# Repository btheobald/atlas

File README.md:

View this project on [CADLAB.io](https://cadlab.io/project/23699). 

# atlas

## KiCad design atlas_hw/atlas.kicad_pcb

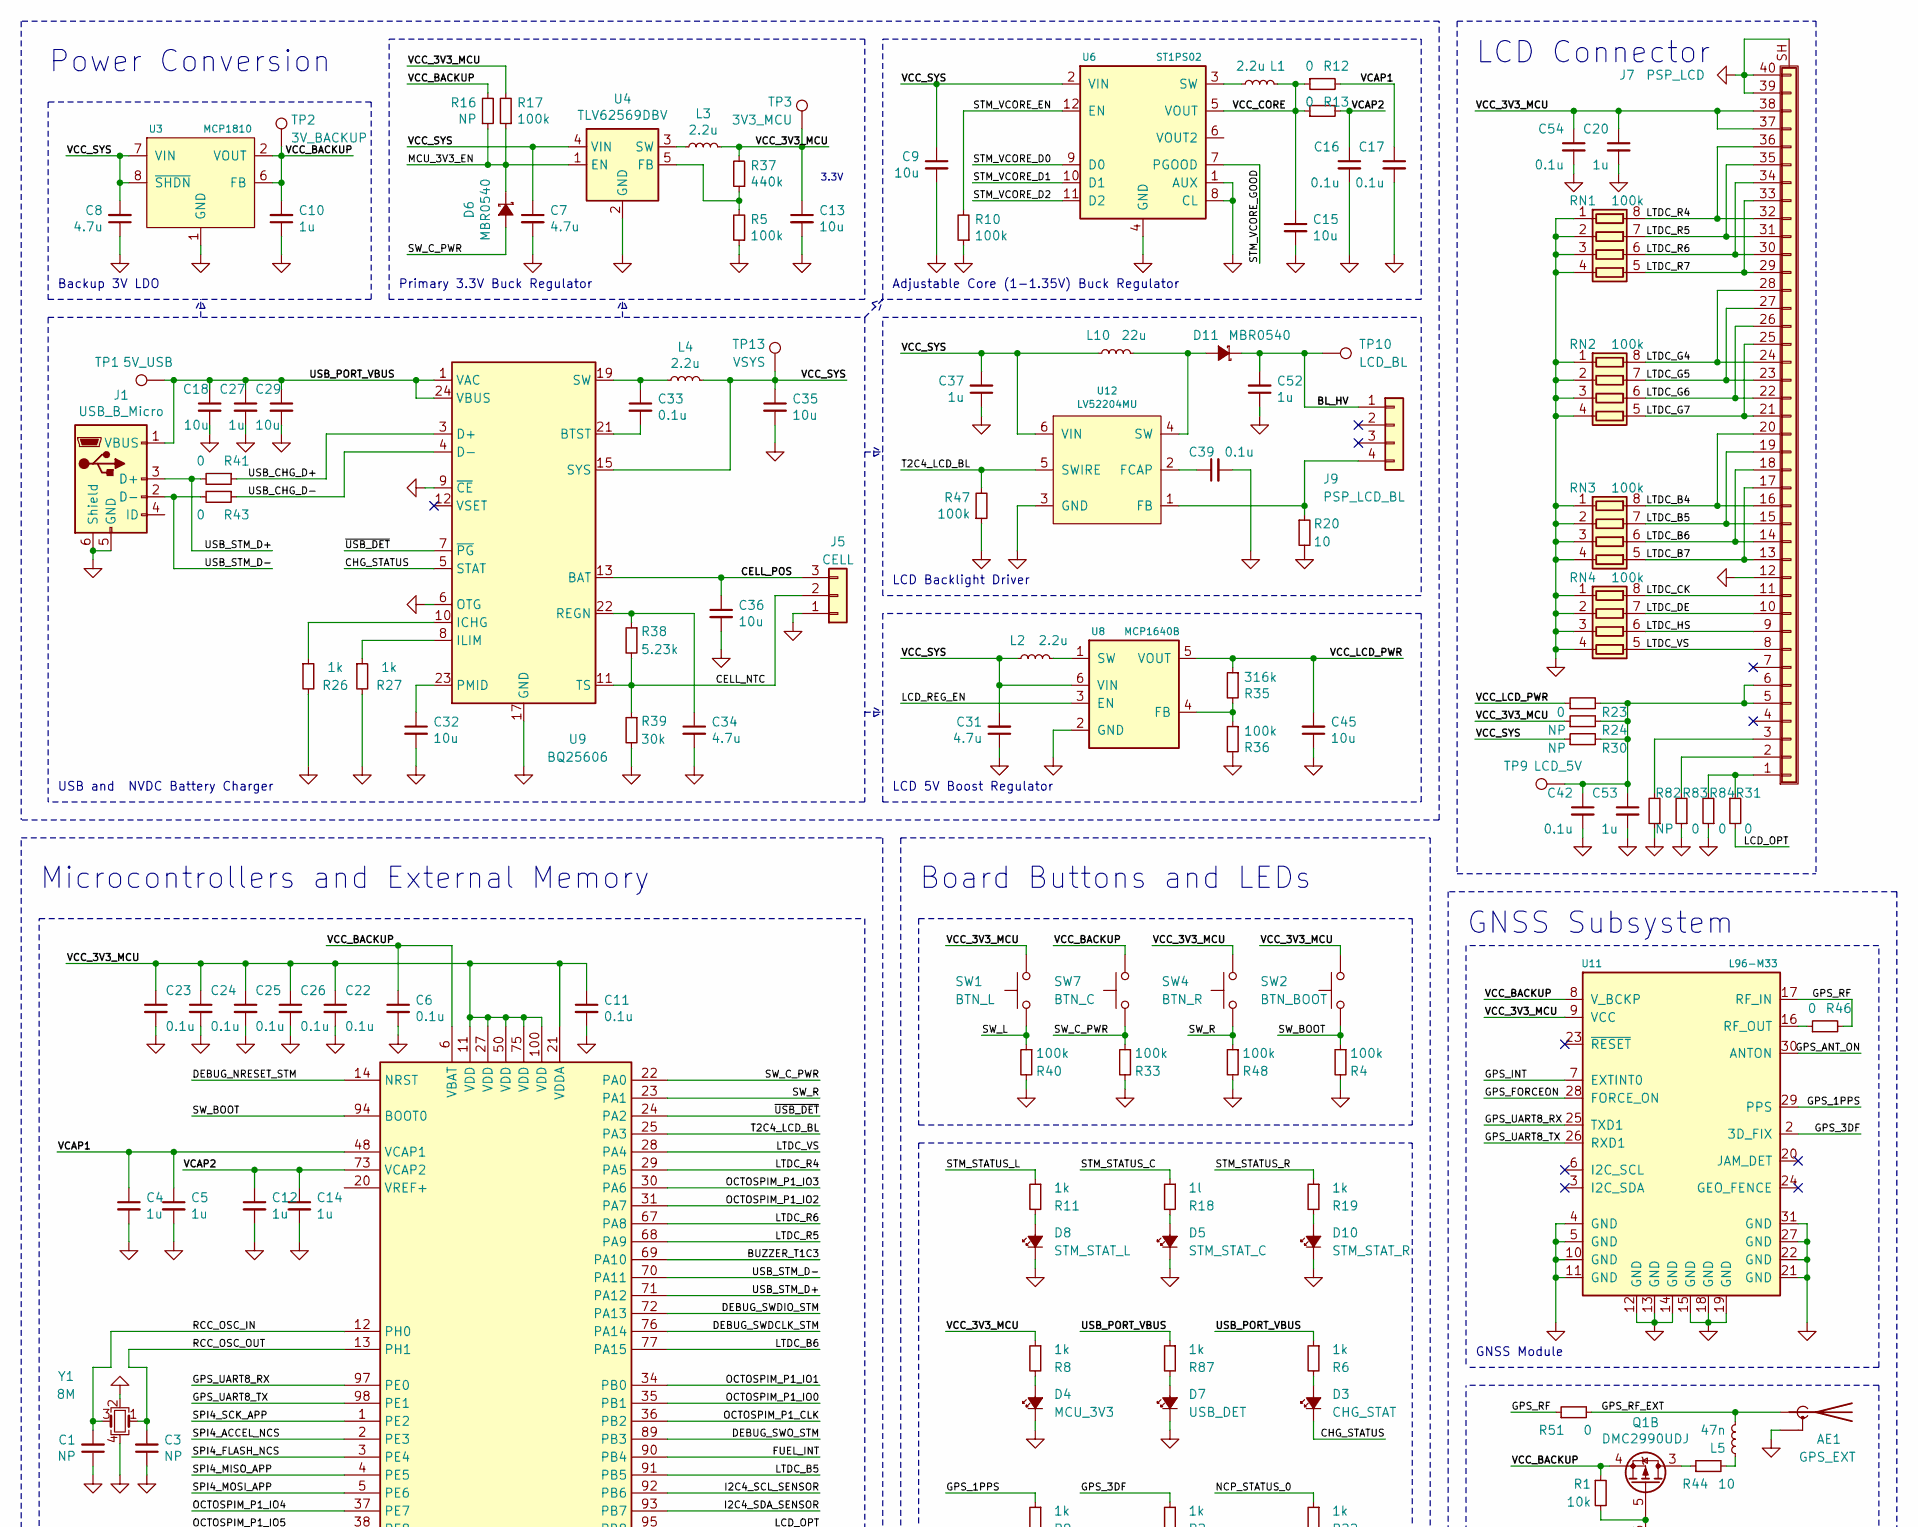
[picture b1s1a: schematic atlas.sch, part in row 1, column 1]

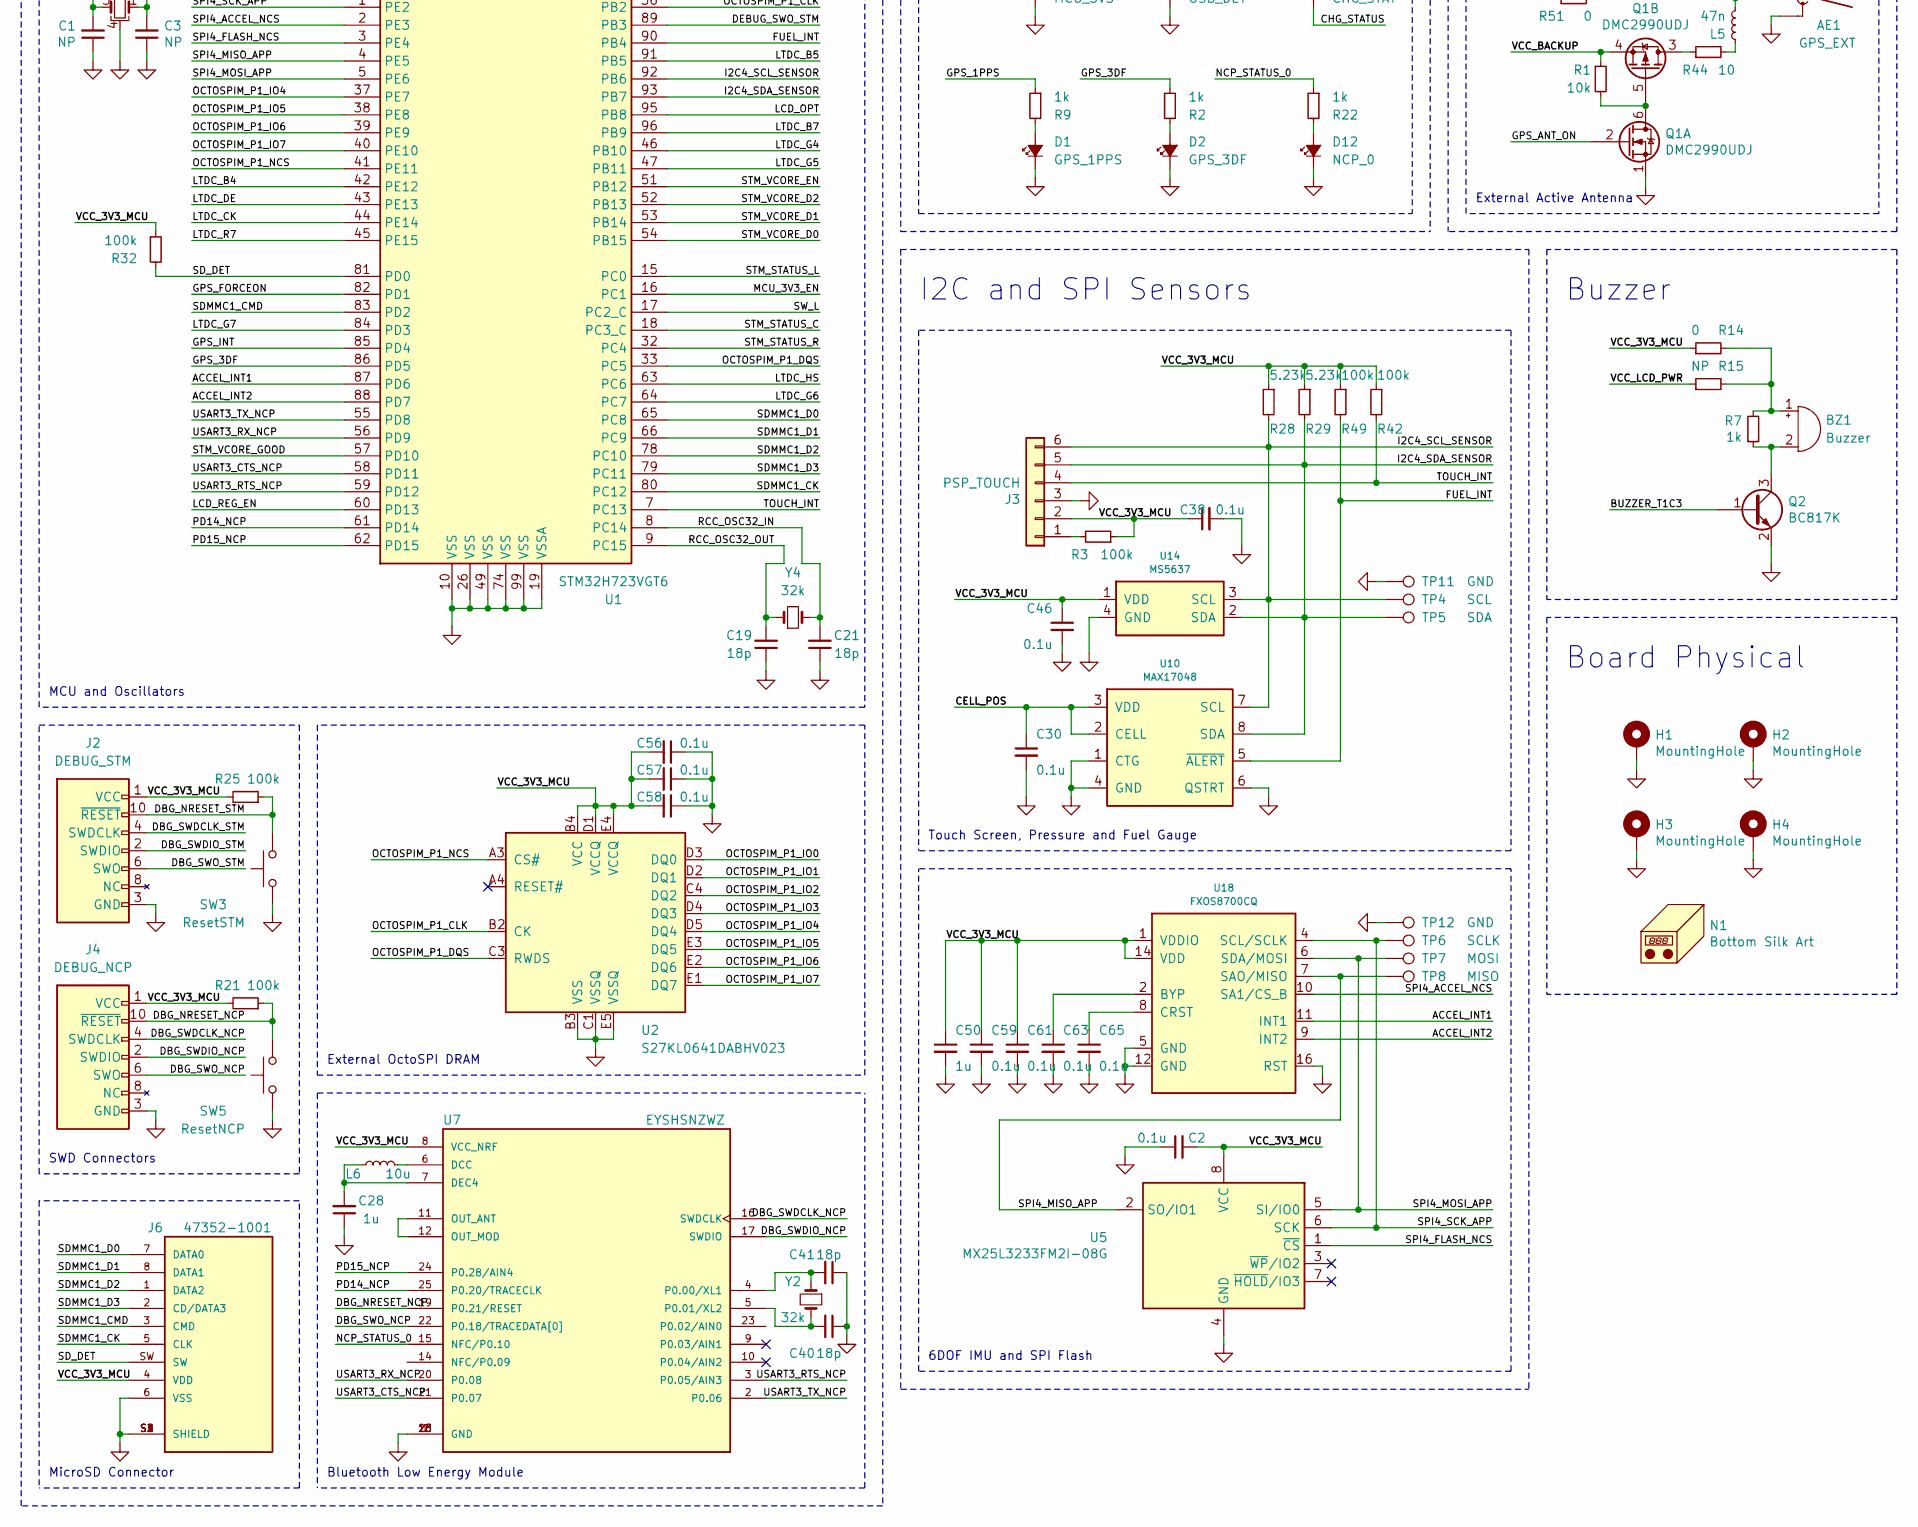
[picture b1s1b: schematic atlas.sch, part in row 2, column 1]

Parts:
AE1: GPS_EXT; U.FL_Hirose_U.FL-R-SMT-1_Vertical
BZ1: Buzzer; PKLCS1212
C1, C3: NP; C_0402_1005Metric
C2, C6, C11, C16, C17, C22, C23, C24, C25, C26, C30, C33, C38, C39, C42, C46, C54, C56, C57, C58, C59, C61, C63, C65: 0.1u; C_0402_1005Metric
C4, C5, C10, C12, C14, C20, C27, C28, C37, C50, C52, C53: 1u; C_0603_1608Metric
C7, C8, C31, C34: 4.7u; C_0805_2012Metric
C9, C13, C15, C18, C29, C32, C35, C36, C45: 10u; C_0805_2012Metric
C19, C21, C40, C41: 18p; C_0402_1005Metric
D1: GPS_1PPS; LED_0805_2012Metric
D2: GPS_3DF; LED_0805_2012Metric
D3: CHG_STAT; LED_0805_2012Metric
D4: MCU_3V3; LED_0805_2012Metric
D5: STM_STAT_C; LED_0805_2012Metric
D6, D11: MBR0540; D_SOD-123
D7: USB_DET; LED_0805_2012Metric
D8: STM_STAT_L; LED_0805_2012Metric
D10: STM_STAT_R; LED_0805_2012Metric
D12: NCP_0; LED_0805_2012Metric
H1, H2, H3, H4: MountingHole; MountingHole_2.2mm_M2_Pad_Via
J1: USB_B_Micro; USB_Micro-B_Molex_47346-0001
J2: DEBUG_STM; PinHeader_2x05_P1.27mm_Vertical_SMD
J3: PSP_TOUCH; TE_2328702-6
J4: DEBUG_NCP; PinHeader_2x05_P1.27mm_Vertical_SMD
J5: CELL; PinHeader_1x03_P1.00mm_Vertical
J6: 47352-1001; MOLEX_47352-1001; PARTREV K
J7: PSP_LCD; J_SMD_4-1734839-0-40_0.5_25.43_5.1_2.05
J9: PSP_LCD_BL; SFV4R-1STE1LF
L1, L2, L3, L4: 2.2u; L_Wuerth_MAPI-2510
L5: 47n; L_0402_1005Metric
L6: 10u; L_Wuerth_MAPI-2510
L10: 22u; L_Bourns-SRN4018
N1: Bottom Silk Art; europeart
Q1: DMC2990UDJ; SOT-363_SC-70-6
Q2: BC817K; SOT-23
R1: 10k; R_0402_1005Metric
R2, R6, R7, R8, R9, R11, R19, R22, R26, R27, R87: 1k; R_0603_1608Metric
R3, R4, R5, R10, R17, R21, R25, R32, R33, R36, R40, R42, R47, R48, R49: 100k; R_0603_1608Metric
R12, R13, R14, R23: 0; SolderJumper-2_P1.3mm_Open_TrianglePad1.0x1.5mm
R15, R24, R30: NP; SolderJumper-2_P1.3mm_Open_TrianglePad1.0x1.5mm
R16: NP; R_0603_1608Metric
R18: 1l; R_0603_1608Metric
R20, R44: 10; R_0603_1608Metric
R28, R29, R38: 5.23k; R_0603_1608Metric
R31, R46, R51, R83, R84: 0; R_0402_1005Metric
R35: 316k; R_0603_1608Metric
R37: 440k; R_0603_1608Metric
R39: 30k; R_0603_1608Metric
R41, R43: 0; R_0603_1608Metric
R82: NP; R_0402_1005Metric
RN1, RN2, RN3, RN4: 100k; R_Array_Concave_4x0402
SW1: BTN_L; SW_SPST_PTS810
SW2: BTN_BOOT; SW_SPST_PTS810
SW3: ResetSTM; SW_SPST_PTS810
SW4: BTN_R; SW_SPST_PTS810
SW5: ResetNCP; SW_SPST_PTS810
SW7: BTN_C; SW_SPST_PTS810
TP1: 5V_USB; TestPoint_THTPad_D1.0mm_Drill0.5mm
TP2: 3V_BACKUP; TestPoint_THTPad_D1.0mm_Drill0.5mm
TP3: 3V3_MCU; TestPoint_THTPad_D1.0mm_Drill0.5mm
TP4: SCL; TestPoint_THTPad_D1.0mm_Drill0.5mm
TP5: SDA; TestPoint_THTPad_D1.0mm_Drill0.5mm
TP6: SCLK; TestPoint_THTPad_D1.0mm_Drill0.5mm
TP7: MOSI; TestPoint_THTPad_D1.0mm_Drill0.5mm
TP8: MISO; TestPoint_THTPad_D1.0mm_Drill0.5mm
TP9: LCD_5V; TestPoint_THTPad_D1.0mm_Drill0.5mm
TP10: LCD_BL; TestPoint_THTPad_D1.0mm_Drill0.5mm
TP11, TP12: GND; TestPoint_THTPad_D1.0mm_Drill0.5mm
TP13: VSYS; TestPoint_THTPad_D1.0mm_Drill0.5mm
U1: STM32H723VGT6; LQFP-100_14x14mm_P0.5mm
U2: S27KL0641DABHV023; BGA-25_5x5_6.0x8.0mm
U3: MCP1810; DFN-8-1EP_2x2mm_P0.5mm_EP0.9x1.5mm
U4: TLV62569DBV; SOT-23-5
U5: MX25L3233FM2I-08G; SSOP-8_5.25x5.24mm_P1.27mm
U6: ST1PS02; TQFN-12_1.7x2.0mm_P0.4mm
U7: EYSHSNZWZ; XCVR_EYSHSNZWZ; PARTREV 1.2
U8: MCP1640B; SOT-23-6
U9: BQ25606; WQFN-24-1EP_4x4mm_P0.5mm_EP2.7x2.7mm
U10: MAX17048; DFN-8-1EP_2x2mm_P0.5mm_EP0.9x1.5mm
U11: L96-M33; L96
U12: LV52204MU; DFN-6-1EP_2x2mm_P0.65mm_EP1x1.6mm
U14: MS5637; QFN-4_3x3_Pitch2mm
U18: FXOS8700CQ; LGA-16_3x3mm_P0.5mm_LayoutBorder3x5y
Y1: 8M; Crystal_SMD_3225-4Pin_3.2x2.5mm
Y2, Y4: 32k; Crystal_SMD_MicroCrystal_CC7V-T1A-2Pin_3.2x1.5mm

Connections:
/ACCEL_INT1: U1.87 (PD6), U18.11 (INT1)
/ACCEL_INT2: U1.88 (PD7), U18.9 (INT2)
/BL_HV: C52.2, D11.1 (K), J9.1, TP10.1
/BUZZER_T1C3: Q2.1 (B), U1.69 (PA10)
/CELL_NTC: J5.2, R38.2, R39.1, U9.11 (TS)
/CELL_POS: C30.1, C36.1, J5.3, U9.13 (BAT), U9.14 (BAT), U10.2 (CELL), U10.3 (VDD)
/CHG_STATUS: D3.1 (K), U9.5 (STAT)
/DBG_NRESET_NCP: J4.10 (~RESET~), R21.1, SW5.1, U7.19 (P0.21/RESET)
/DBG_NRESET_STM: J2.10 (~RESET~), R25.1, SW3.1
/DBG_SWDCLK_NCP: J4.4 (SWDCLK), U7.16 (SWDCLK)
/DBG_SWDCLK_STM: J2.4 (SWDCLK)
/DBG_SWDIO_NCP: J4.2 (SWDIO), U7.17 (SWDIO)
/DBG_SWDIO_STM: J2.2 (SWDIO)
/DBG_SWO_NCP: J4.6 (SWO), U7.22 (P0.18/TRACEDATA[0])
/DBG_SWO_STM: J2.6 (SWO)
/DEBUG_NRESET_STM: U1.14 (NRST)
/DEBUG_SWDCLK_STM: U1.76 (PA14)
/DEBUG_SWDIO_STM: U1.72 (PA13)
/DEBUG_SWO_STM: U1.89 (PB3)
/FUEL_INT: R49.2, U1.90 (PB4), U10.5 (~ALERT)
/GPS_1PPS: R9.1, U11.29 (PPS)
/GPS_3DF: R2.1, U1.86 (PD5), U11.2 (3D_FIX)
/GPS_ANT_ON: Q1.2 (G), U11.30 (ANTON)
/GPS_FORCEON: U1.82 (PD1), U11.28 (FORCE_ON)
/GPS_INT: U1.85 (PD4), U11.7 (EXTINT0)
/GPS_RF: R46.2, R51.1, U11.17 (RF_IN)
/GPS_RF_EXT: AE1.1 (A), L5.1, R51.2
/GPS_UART8_RX: U1.97 (PE0), U11.25 (TXD1)
/GPS_UART8_TX: U1.98 (PE1), U11.26 (RXD1)
/I2C4_SCL_SENSOR: J3.6, R28.2, TP4.1, U1.92 (PB6), U10.7 (SCL), U14.3 (SCL)
/I2C4_SDA_SENSOR: J3.5, R29.2, TP5.1, U1.93 (PB7), U10.8 (SDA), U14.2 (SDA)
/LCD_OPT: R31.2, U1.95 (PB8)
/LCD_REG_EN: U1.60 (PD13), U8.3 (EN)
/LTDC_B4: J7.16, J7.20, RN3.8 (R1.2), U1.42 (PE12)
/LTDC_B5: J7.15, J7.19, RN3.7 (R2.2), U1.91 (PB5)
/LTDC_B6: J7.14, J7.18, RN3.6 (R3.2), U1.77 (PA15)
/LTDC_B7: J7.13, J7.17, RN3.5 (R4.2), U1.96 (PB9)
/LTDC_CK: J7.11, RN4.8 (R1.2), U1.44 (PE14)
/LTDC_DE: J7.10, RN4.7 (R2.2), U1.43 (PE13)
/LTDC_G4: J7.24, J7.28, RN2.8 (R1.2), U1.46 (PB10)
/LTDC_G5: J7.23, J7.27, RN2.7 (R2.2), U1.47 (PB11)
/LTDC_G6: J7.22, J7.26, RN2.6 (R3.2), U1.64 (PC7)
/LTDC_G7: J7.21, J7.25, RN2.5 (R4.2), U1.84 (PD3)
/LTDC_HS: J7.9, RN4.6 (R3.2), U1.63 (PC6)
/LTDC_R4: J7.32, J7.36, RN1.8 (R1.2), U1.29 (PA5)
/LTDC_R5: J7.31, J7.35, RN1.7 (R2.2), U1.68 (PA9)
/LTDC_R6: J7.30, J7.34, RN1.6 (R3.2), U1.67 (PA8)
/LTDC_R7: J7.29, J7.33, RN1.5 (R4.2), U1.45 (PE15)
/LTDC_VS: J7.8, RN4.5 (R4.2), U1.28 (PA4)
/MCU_3V3_EN: D6.1 (K), R16.1, R17.1, U1.16 (PC1), U4.1 (EN)
/NCP_STATUS_0: R22.1, U7.15 (NFC/P0.10)
/OCTOSPIM_P1_CLK: U1.36 (PB2), U2.B2 (CK)
/OCTOSPIM_P1_DQS: U1.33 (PC5), U2.C3 (RWDS)
/OCTOSPIM_P1_IO0: U1.35 (PB1), U2.D3 (DQ0)
/OCTOSPIM_P1_IO1: U1.34 (PB0), U2.D2 (DQ1)
/OCTOSPIM_P1_IO2: U1.31 (PA7), U2.C4 (DQ2)
/OCTOSPIM_P1_IO3: U1.30 (PA6), U2.D4 (DQ3)
/OCTOSPIM_P1_IO4: U1.37 (PE7), U2.D5 (DQ4)
/OCTOSPIM_P1_IO5: U1.38 (PE8), U2.E3 (DQ5)
/OCTOSPIM_P1_IO6: U1.39 (PE9), U2.E2 (DQ6)
/OCTOSPIM_P1_IO7: U1.40 (PE10), U2.E1 (DQ7)
/OCTOSPIM_P1_NCS: U1.41 (PE11), U2.A3 (CS#)
/PD14_NCP: U1.61 (PD14), U7.25 (P0.20/TRACECLK)
/PD15_NCP: U1.62 (PD15), U7.24 (P0.28/AIN4)
/RCC_OSC32_IN: C21.2, U1.8 (PC14), Y4.2
/RCC_OSC32_OUT: C19.2, U1.9 (PC15), Y4.1
/RCC_OSC_IN: C1.2, U1.12 (PH0), Y1.3
/RCC_OSC_OUT: C3.2, U1.13 (PH1), Y1.1
/SDMMC1_CK: J6.5 (CLK), U1.80 (PC12)
/SDMMC1_CMD: J6.3 (CMD), U1.83 (PD2)
/SDMMC1_D0: J6.7 (DATA0), U1.65 (PC8)
/SDMMC1_D1: J6.8 (DATA1), U1.66 (PC9)
/SDMMC1_D2: J6.1 (DATA2), U1.78 (PC10)
/SDMMC1_D3: J6.2 (CD/DATA3), U1.79 (PC11)
/SD_DET: J6.SW, R32.2, U1.81 (PD0)
/SPI4_ACCEL_NCS: U1.2 (PE3), U18.10 (SA1/CS_B)
/SPI4_FLASH_NCS: U1.3 (PE4), U5.1 (~CS)
/SPI4_MISO_APP: TP8.1, U1.4 (PE5), U5.2 (SO/IO1), U18.7 (SAO/MISO)
/SPI4_MOSI_APP: TP7.1, U1.5 (PE6), U5.5 (SI/IO0), U18.6 (SDA/MOSI)
/SPI4_SCK_APP: TP6.1, U1.1 (PE2), U5.6 (SCK), U18.4 (SCL/SCLK)
/STM_STATUS_C: R18.1, U1.18 (PC3_C)
/STM_STATUS_L: R11.1, U1.15 (PC0)
/STM_STATUS_R: R19.1, U1.32 (PC4)
/STM_VCORE_D0: U1.54 (PB15), U6.9 (D0)
/STM_VCORE_D1: U1.53 (PB14), U6.10 (D1)
/STM_VCORE_D2: U1.52 (PB13), U6.11 (D2)
/STM_VCORE_EN: R10.2, U1.51 (PB12), U6.12 (EN)
/STM_VCORE_GOOD: U1.57 (PD10), U6.7 (PGOOD)
/SW_BOOT: R4.1, SW2.2, U1.94 (BOOT0)
/SW_C_PWR: D6.2 (A), R33.1, SW7.2, U1.22 (PA0)
/SW_L: R40.1, SW1.2, U1.17 (PC2_C)
/SW_R: R48.1, SW4.2, U1.23 (PA1)
/T2C4_LCD_BL: R47.2, U1.25 (PA3), U12.5 (SWIRE)
/TOUCH_INT: J3.4, R42.2, U1.7 (PC13)
/USART3_CTS_NCP: U1.58 (PD11), U7.21 (P0.07)
/USART3_RTS_NCP: U1.59 (PD12), U7.3 (P0.05/AIN3)
/USART3_RX_NCP: U1.56 (PD9), U7.20 (P0.08)
/USART3_TX_NCP: U1.55 (PD8), U7.2 (P0.06)
/USB_CHG_D+: R41.1, U9.3 (D+)
/USB_CHG_D-: R43.1, U9.4 (D-)
/USB_PORT_VBUS: C18.1, C27.1, C29.1, J1.1 (VBUS), R6.1, R87.1, TP1.1, U9.1 (VAC), U9.24 (VBUS)
/USB_STM_D+: J1.3 (D+), R41.2, U1.71 (PA12)
/USB_STM_D-: J1.2 (D-), R43.2, U1.70 (PA11)
/VCAP1: C4.1, C5.1, C17.1, R12.2, U1.48 (VCAP1)
/VCAP2: C12.1, C14.1, C16.1, R13.2, U1.73 (VCAP2)
/VCC_3V3_MCU: C2.2, C11.1, C13.1, C20.1, C22.1, C23.1, C24.1, C25.1, C26.1, C38.1, C46.1, C50.1, C54.1, C56.2, C57.2, C58.2, C59.1, C61.1, J2.1 (VCC), J3.2, J4.1 (VCC), J6.4 (VDD), J7.37, J7.38, L3.2, R3.1, R8.1, R14.1, R17.2, R21.2, R24.1, R25.2, R28.1, R29.1, R32.1, R37.2, R42.1, R49.1, SW1.1, SW2.1, SW4.1, TP3.1, U1.11 (VDD), U1.21 (VDDA), U1.27 (VDD), U1.50 (VDD), U1.75 (VDD), U1.100 (VDD), U2.B4 (VCC), U2.D1 (VCCQ), U2.E4 (VCCQ), U5.8 (VCC), U7.8 (VCC_NRF), U11.9 (VCC), U14.1 (VDD), U18.1 (VDDIO), U18.14 (VDD)
/VCC_BACKUP: C6.1, C10.2, Q1.4 (S), R1.1, R16.2, SW7.1, TP2.1, U1.6 (VBAT), U3.2 (VOUT), U3.6 (FB), U11.8 (V_BCKP)
/VCC_CORE: C15.1, L1.2, R12.1, R13.1, U6.5 (VOUT)
/VCC_LCD_PWR: C45.2, R15.1, R23.1, R35.1, U8.5 (VOUT)
/VCC_SYS: C7.1, C8.2, C9.1, C31.2, C35.1, C37.2, L2.1, L4.2, L10.1, R30.1, TP13.1, U3.7 (VIN), U3.8 (~SHDN), U4.4 (VIN), U6.2 (VIN), U8.6 (VIN), U9.15 (SYS), U9.16 (SYS), U12.6 (VIN)
/~USB_DET: U1.24 (PA2), U9.7 (~PG)
GND: AE1.2 (Shield), C1.1, C2.1, C3.1, C4.2, C5.2, C6.2, C7.2, C8.1, C9.2, C10.1, C11.2, C12.2, C13.2, C14.2, C15.2, C16.2, C17.2, C18.2, C19.1, C20.2, C21.1, C22.2, C23.2, C24.2, C25.2, C26.2, C27.2, C28.1, C29.2, C30.2, C31.1, C32.2, C34.2, C35.2, C36.2, C37.1, C38.2, C39.2, C40.1, C41.1, C42.2, C45.1, C46.2, C50.2, C52.1, C53.2, C54.2, C56.1, C57.1, C58.1, C59.2, C61.2, C63.2, C65.2, D1.1 (K), D2.1 (K), D4.1 (K), D5.1 (K), D7.1 (K), D8.1 (K), D10.1 (K), D12.1 (K), H1.1, H2.1, H3.1, H4.1, J1.5 (GND), J1.6 (Shield), J2.3 (GND), J2.5 (GND), J2.9 (GND), J3.3, J4.3 (GND), J4.5 (GND), J4.9 (GND), J5.1, J6.6 (VSS), J6.S1 (SHIELD), J6.S2 (SHIELD), J6.S3 (SHIELD), J6.S4 (SHIELD), J7.12, J7.39, J7.40, J7.SH (Shield), Q1.1 (S), Q2.2 (E), R4.2, R5.1, R10.1, R20.2, R26.2, R27.2, R33.2, R36.2, R39.2, R40.2, R47.1, R48.2, R82.1, R83.1, R84.1, RN1.1 (R1.1), RN1.2 (R2.1), RN1.3 (R3.1), RN1.4 (R4.1), RN2.1 (R1.1), RN2.2 (R2.1), RN2.3 (R3.1), RN2.4 (R4.1), RN3.1 (R1.1), RN3.2 (R2.1), RN3.3 (R3.1), RN3.4 (R4.1), RN4.1 (R1.1), RN4.2 (R2.1), RN4.3 (R3.1), RN4.4 (R4.1), SW3.2, SW5.2, TP11.1, TP12.1, U1.10 (VSS), U1.19 (VSSA), U1.26 (VSS), U1.49 (VSS), U1.74 (VSS), U1.99 (VSS), U2.B3 (VSS), U2.C1 (VSSQ), U2.E5 (VSSQ), U3.1 (GND), U3.9 (EP), U4.2 (GND), U5.4 (GND), U6.1 (AUX), U6.4 (GND), U6.8 (CL), U7.1 (GND), U7.13 (GND), U7.18 (GND), U7.26 (GND), U8.2 (GND), U9.6 (OTG), U9.9 (~CE), U9.17 (GND), U9.25 (GND), U10.1 (CTG), U10.4 (GND), U10.6 (QSTRT), U10.9 (PAD), U11.4 (GND), U11.5 (GND), U11.10 (GND), U11.11 (GND), U11.12 (GND), U11.13 (GND), U11.14 (GND), U11.15 (GND), U11.18 (GND), U11.19 (GND), U11.21 (GND), U11.22 (GND), U11.27 (GND), U11.31 (GND), U12.3 (GND), U12.7 (PAD), U14.4 (GND), U18.3 (f), U18.5 (GND), U18.12 (GND), U18.13 (RESERVED)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
unnamed: BZ1.1 (-), R7.2, R14.2, R15.2
unnamed: BZ1.2 (+), Q2.3 (C), R7.1
unnamed: C28.2, L6.1, U7.7 (DEC4)
unnamed: C32.1, U9.23 (PMID)
unnamed: C33.1, L4.1, U9.19 (SW), U9.20 (SW)
unnamed: C33.2, U9.21 (BTST)
unnamed: C34.1, R38.1, U9.22 (REGN)
unnamed: C39.1, U12.2 (FCAP)
unnamed: C40.2, U7.5 (P0.01/XL2), Y2.2
unnamed: C41.2, U7.4 (P0.00/XL1), Y2.1
unnamed: C42.1, C53.1, J7.5, J7.6, R23.2, R24.2, R30.2, TP9.1
unnamed: C63.1, U18.2 (BYP)
unnamed: C65.1, U18.8 (CRST)
unnamed: D1.2 (A), R9.2
unnamed: D2.2 (A), R2.2
unnamed: D3.2 (A), R6.2
unnamed: D4.2 (A), R8.2
unnamed: D5.2 (A), R18.2
unnamed: D7.2 (A), R87.2
unnamed: D8.2 (A), R11.2
unnamed: D10.2 (A), R19.2
unnamed: D11.2 (A), L10.2, U12.4 (SW)
unnamed: D12.2 (A), R22.2
unnamed: J3.1, R3.2
unnamed: J7.1, R31.1, R84.2
unnamed: J7.2, R83.2
unnamed: J7.3, R82.2
unnamed: J9.4, R20.1, U12.1 (FB)
unnamed: L1.1, U6.3 (SW)
unnamed: L2.2, U8.1 (SW)
unnamed: L3.1, U4.3 (SW)
unnamed: L5.2, R44.2
unnamed: L6.2, U7.6 (DCC)
unnamed: Q1.3 (D), R44.1
unnamed: Q1.5 (G), Q1.6 (D), R1.2
unnamed: R26.1, U9.10 (ICHG)
unnamed: R27.1, U9.8 (ILIM)
unnamed: R35.2, R36.1, U8.4 (FB)
unnamed: R5.2, R37.1, U4.5 (FB)
unnamed: R46.1, U11.16 (RF_OUT)
unnamed: U7.11 (OUT_ANT), U7.12 (OUT_MOD)

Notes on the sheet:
Board Physical
Buzzer
External Active Antenna
I2C and SPI Sensors
GNSS Module
GNSS Subsystem
LCD Connector
MicroSD Connector
Bluetooth Low Energy Module
Board Buttons and LEDs
External OctoSPI DRAM
SWD Connectors
MCU and Oscillators
Microcontrollers and External Memory
LCD 5V Boost Regulator
LCD Backlight Driver
Adjustable Core (1-1.35V) Buck Regulator
Primary 3.3V Buck Regulator
Backup 3V LDO
USB and NVDC Battery Charger
Power Conversion
3.3V
Touch Screen, Pressure and Fuel Gauge
6DOF IMU and SPI Flash

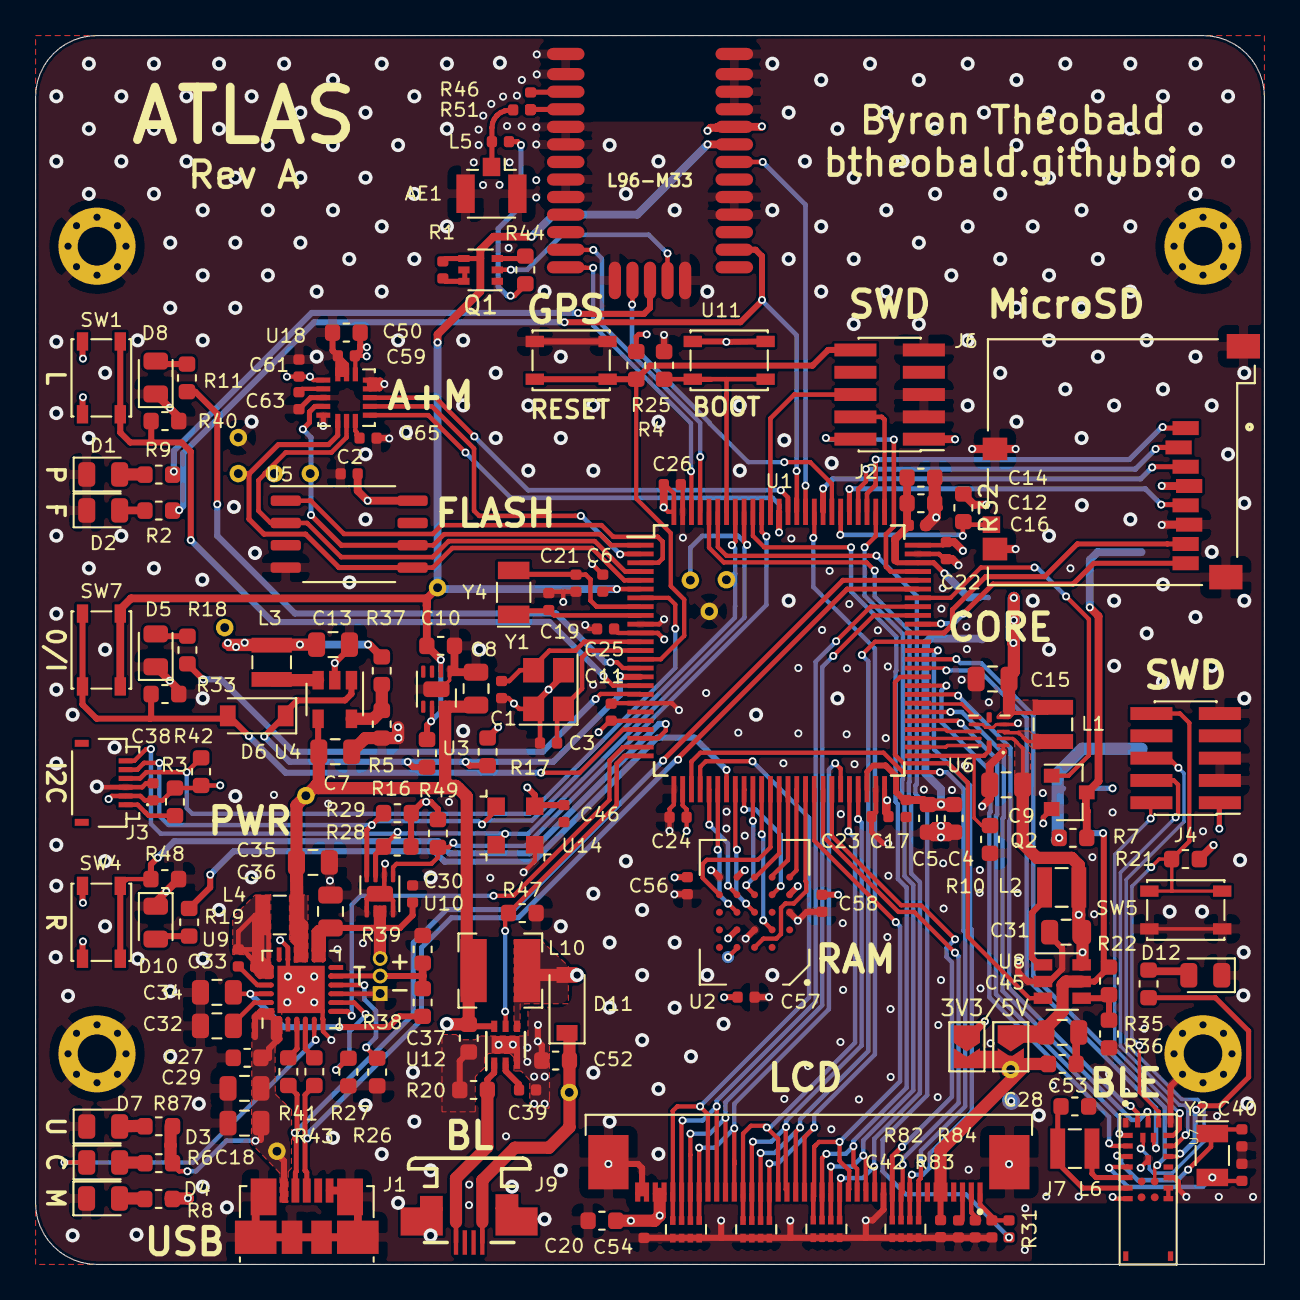
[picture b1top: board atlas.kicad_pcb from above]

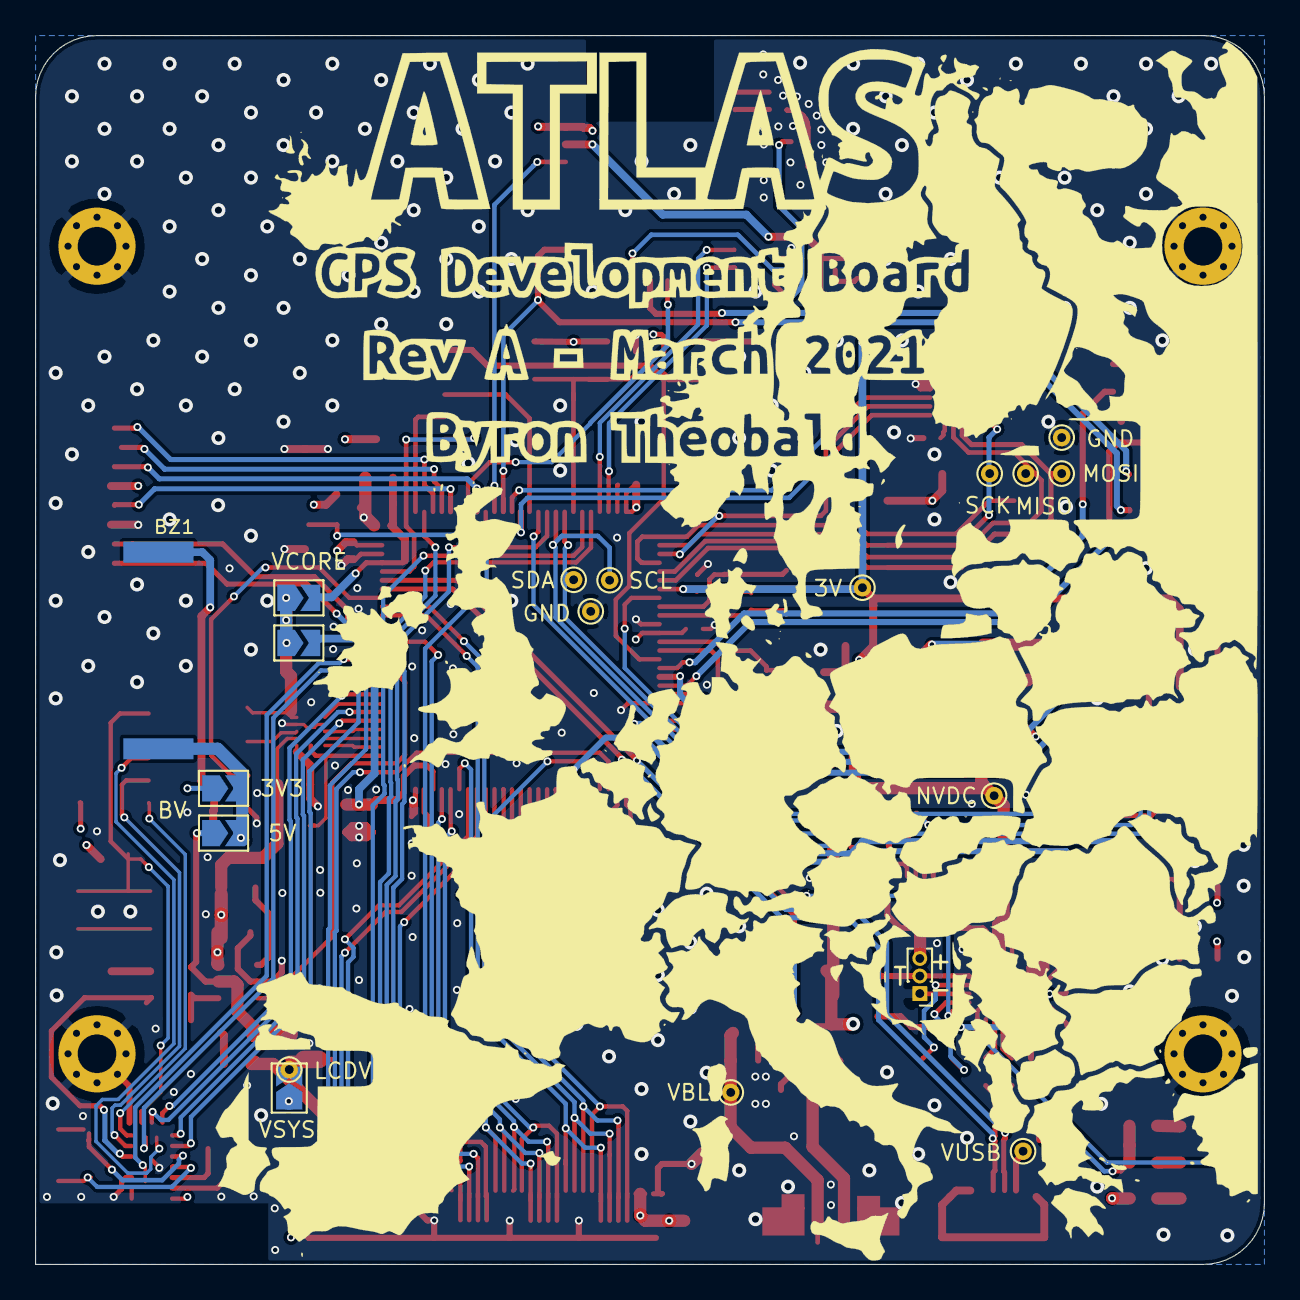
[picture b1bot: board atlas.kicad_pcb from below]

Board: 4 copper layers, 70.0 x 70.0 mm, 182 parts (21 on the bottom side), 146 nets.

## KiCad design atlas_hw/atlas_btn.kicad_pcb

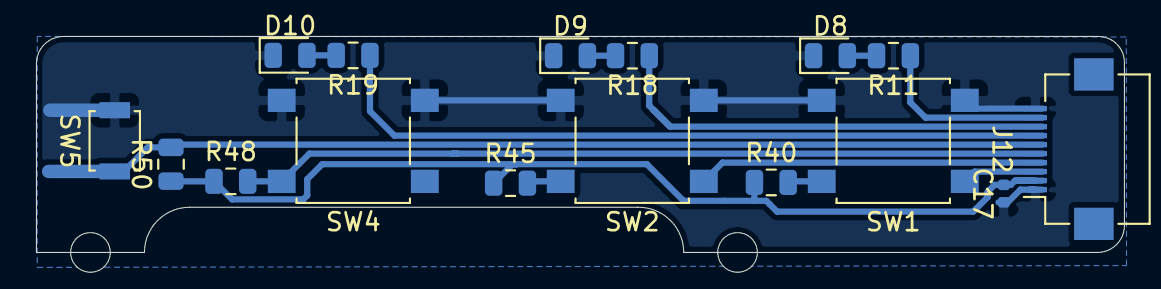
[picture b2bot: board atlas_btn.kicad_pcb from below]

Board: 4 copper layers, 60.4 x 12.0 mm, 16 parts (16 on the bottom side), 12 nets.

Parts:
C17: 0.1u; C_0402_1005Metric
D8: STM_STATUS_L; LED_0805_2012Metric
D9: STM_STATUS_0; LED_0805_2012Metric
D10: STM_STATUS_R; LED_0805_2012Metric
J12: IO_EXT; Hirose_FH12-10S-0.5SH_1x10-1MP_P0.50mm_Horizontal
R11, R18, R19: 1k; R_0805_2012Metric
R40, R45, R48, R50: 100k; R_0805_2012Metric
SW1: BTN_L_EXT; SW_SPST_B3S-1000
SW2: BTN_0_EXT; SW_SPST_B3S-1000
SW4: BTN_R_EXT; SW_SPST_B3S-1000
SW5: BTN_PWR_EXT; SW_SPST_B3U-1000P

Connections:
/STM_STATUS_0_EXT: J12.8, R18.1
/STM_STATUS_L_EXT: J12.9, R11.1
/STM_STATUS_R_EXT: J12.7, R19.1
/SW_0_EXT: J12.4, R45.2, SW2.1
/SW_L_EXT: J12.3, R40.2, SW1.1
/SW_PWR_EXT: J12.6, R50.2, SW5.1
/SW_R_EXT: J12.5, R48.2, SW4.1
/VCC_3V3_EXT: C17.2, J12.2, R40.1, R45.1, R48.1, R50.1
GND: C17.1, D8.1, D9.1, D10.1, J12.1, J12.10, SW1.2, SW2.2, SW4.2, SW5.2
unnamed: D8.2, R11.2
unnamed: D9.2, R18.2
unnamed: D10.2, R19.2

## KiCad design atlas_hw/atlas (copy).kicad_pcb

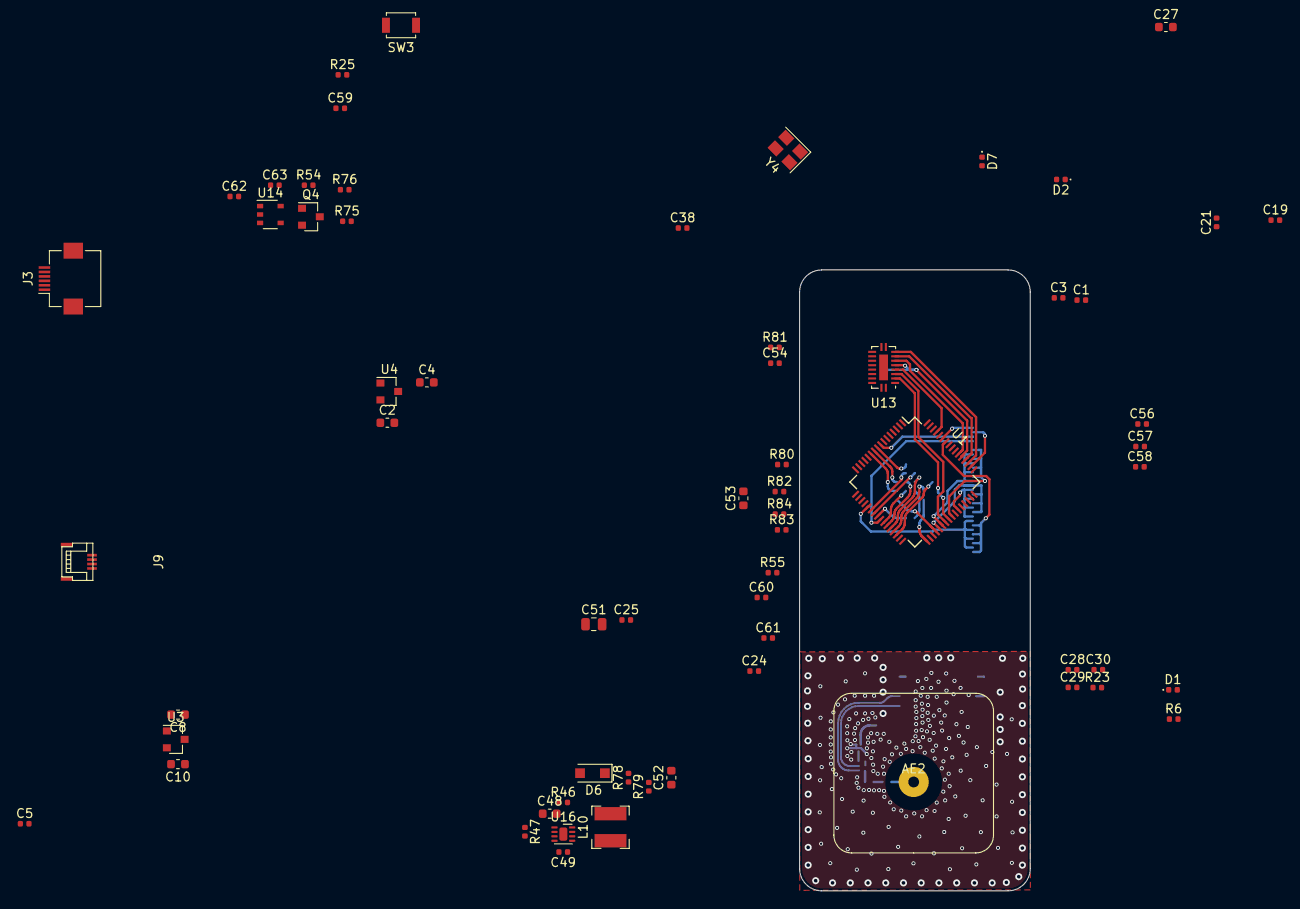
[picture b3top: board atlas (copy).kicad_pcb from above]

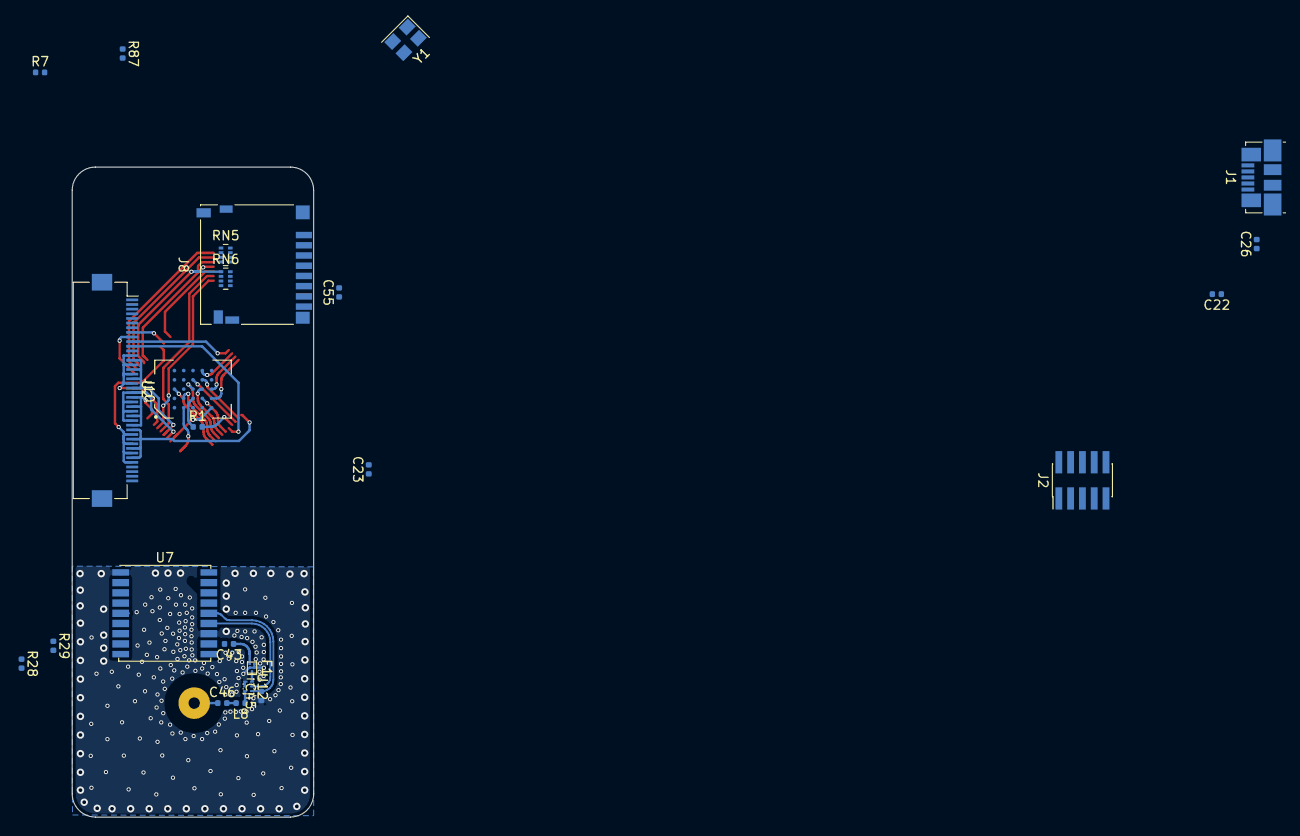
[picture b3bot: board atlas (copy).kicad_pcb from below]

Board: 4 copper layers, 26.0 x 70.0 mm, 87 parts (24 on the bottom side), 85 nets.

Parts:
AE2: 2088900001
C1, C3: NP; C_0402_1005Metric
C2, C4, C8, C10, C27, C48, C52, C53: 1u; C_0603_1608Metric
C5, C22, C23, C24, C25, C26, C28, C29, C30, C38, C45, C49, C54, C55, C56, C57, C58, C59, C60, C61: 0.1u; C_0402_1005Metric
C19, C21: 22p; C_0402_1005Metric
C43, C46: 120p; C_0402_1005Metric
C51: 10u; C_0805_2012Metric
C62, C63: 1u; C_0402_1005Metric
D1: GPS_1PPS; LED_0402_1005Metric
D2: STM_STATUS; LED_0402_1005Metric
D6: D_Schottky_Small_ALT; D_SOD-123F
D7: USB_DETECT; LED_0402_1005Metric
F1: B39162B8813P810; Filter_1109-5_1.1x0.9mm
J1: USB_B_Micro; USB_Micro-B_Molex_47346-0001
J2: DEBUG_STM; PinHeader_2x05_P1.27mm_Vertical_SMD
J3: PSP_TOUCH; Hirose_FH12-6S-0.5SH_1x06-1MP_P0.50mm_Horizontal
J8: Micro_SD_Card_Det; microSD_HC_Hirose_DM3D-SF
J9: PSP_LCD_BL; Kyocera_046298_004_1x04_P0.5mm_Bottom
J10: PSP_LCD; Hirose_FH12-40S-0.5SH_1x40-1MP_P0.50mm_Horizontal
L8: 5n6; L_0402_1005Metric
L10: 3.9n; L_Bourns-SRN4018
Q4: Q_NMOS_DGS; SOT-23
R1: NC; R_0402_1005Metric
R6, R7, R87: 1k; R_0402_1005Metric
R23, R47, R55: 100k; R_0402_1005Metric
R25, R54: 10k; R_0402_1005Metric
R28, R29, R82: NP; R_0402_1005Metric
R46, R80, R81, R83, R84: 0; R_0402_1005Metric
R75: 200k; R_0402_1005Metric
R76: 250k; R_0402_1005Metric
R78, R79: 4.7k; R_0402_1005Metric
RN5, RN6: R_Pack04; R_Array_Concave_4x0402
SW3: ResetSTM; SW_SPST_B3U-1000P
U1: STM32L4A6RGTx; LQFP-64_10x10mm_P0.5mm
U2: W957A8MFYA5I; BGA-25_5x5_6.0x8.0mm
U3: MCP1811B; SOT-23
U4: MCP1812B; SOT-23
U7: Teseo-LIV3F; ublox_MAX
U12: BGU7007; 6-XSON_1.5x1.0mm_0.5mm
U13: LSF0108; WQFN-20-1EP_2.5x4.5mm_P0.5mm_EP1x2.9mm
U14: NPP600SNADJ; TSOP-5_1.65x3.05mm_P0.95mm
U16: PAM2841; DFN-8-1EP_2x2mm_P0.5mm_EP0.9x1.5mm
Y1: 16M; Crystal_SMD_3225-4Pin_3.2x2.5mm
Y4: 32k; Crystal_SMD_3225-4Pin_3.2x2.5mm

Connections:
/DEBUG_NRESET_STM: J2.10, R25.1, SW3.1, U1.7, U2.A4
/DEBUG_SWDCLK_STM: J2.4, U1.49
/DEBUG_SWDIO_STM: J2.2, U1.46
/GPS_1PPS: D1.2, U7.4
/GPS_ANT_OFF: U7.13, U12.5
/GPS_RESET: R23.2, U1.60, U7.9
/GPS_VCC_RF: C45.2, U7.14, U12.4
/GPS_WAKEUP: U1.62, U7.5
/I2C_SCL_SENSOR: J3.1, R28.2, U1.34, U7.17
/I2C_SDA_SENSOR: J3.2, R29.2, U1.35, U7.16
/LTDC_B6: J10.14, J10.16, J10.18, J10.20, U1.38
/LTDC_B7: J10.13, J10.15, J10.17, J10.19, U1.41
/LTDC_CK: J10.11, U1.25
/LTDC_DE: J10.10, U1.8
/LTDC_G6: J10.22, J10.24, J10.26, J10.28, U1.43
/LTDC_G7: J10.21, J10.23, J10.25, J10.27, U1.37
/LTDC_HS: J10.9, U1.50
/LTDC_R6: J10.30, J10.32, J10.34, J10.36, U1.58
/LTDC_R7: J10.29, J10.31, J10.33, J10.35, U1.21
/LTDC_VS: J10.8, U1.59
/OCTOSPIM_P1_CLK: U1.29, U2.B2
/OCTOSPIM_P1_DQS: U1.28, U2.C3
/OCTOSPIM_P1_IO0: U1.27, U2.D3
/OCTOSPIM_P1_IO1: U1.26, U2.D2
/OCTOSPIM_P1_IO2: U1.23, U2.C4
/OCTOSPIM_P1_IO3: U1.22, U2.D4
/OCTOSPIM_P1_IO4: U1.9, U2.D5
/OCTOSPIM_P1_IO5: U1.10, U2.E3
/OCTOSPIM_P1_IO6: U1.11, U2.E2
/OCTOSPIM_P1_IO7: U1.36, U2.E1
/OCTOSPIM_P1_NCLK: U1.33, U2.B1
/OCTOSPIM_P1_NCS: U1.30, U2.A3
/OCTOSPIM_P2_NCS: R1.2, U1.24
/RCC_OSC32_IN: C21.2, U1.3, Y4.2
/RCC_OSC32_OUT: C19.2, U1.4, Y4.1
/RCC_OSC_IN: C1.2, U1.5, Y1.1
/RCC_OSC_OUT: C3.2, U1.6, Y1.2
/SDMMC1_CK: RN6.1, U1.53, U13.6
/SDMMC1_CKIN: U1.61, U13.5
/SDMMC1_CMD: RN5.4, U1.54, U13.7
/SDMMC1_D0: RN6.3, U1.39, U13.4
/SDMMC1_D1: RN6.4, U1.40, U13.3
/SDMMC1_D2: RN5.1, U1.51, U13.9
/SDMMC1_D3: RN5.2, U1.52, U13.8
/SDMMC1_DET: J8.9, R55.1
/SD_CLK: J8.5, RN6.8, U13.15, U13.16
/SD_CMD: J8.3, RN5.5, U13.14
/SD_D0: J8.7, RN6.6, U13.17
/SD_D1: J8.8, RN6.5, U13.18
/SD_D2: J8.1, RN5.8, U13.12
/SD_D3: J8.2, RN5.7, U13.13
/STM_STATUS: D2.2, U1.2
/TIM4_CH3_LCD_BL_PWM: R47.2, U16.3
/USB_PORT_VBUS: C2.2, C8.2, C27.1, D7.2, J1.1, R46.2, U3.1, U4.1
/USB_STM_D+: J1.2, U1.45
/USB_STM_D-: J1.3, U1.44
/VCC_BACKUP: C30.1, U7.6
/VCC_MCU: C10.2, U3.2
/VCC_MCU_3V3: C5.1, C22.1, C23.1, C24.1, C25.1, C26.1, C28.1, C29.1, C38.1, C56.2, C57.2, C58.2, C59.1, J2.1, J3.4, R25.2, R28.1, R29.1, R55.2, R81.2, U1.1, U1.13, U1.19, U1.32, U1.48, U1.64, U2.B4, U2.D1, U2.E4, U7.7, U7.8, U13.2
/VCC_SD_3V3: C4.2, C61.1, C62.1, J8.4, U4.2, U14.1, U14.3
/VDD_SD_IO_3V3_1V8: C60.1, C63.1, R75.2, U13.19, U13.20, U14.5
GND: C1.1, C2.1, C3.1, C4.1, C5.2, C8.1, C10.1, C19.1, C21.1, C22.2, C23.2, C24.2, C25.2, C26.2, C27.2, C28.2, C29.2, C30.2, C38.2, C45.1, C48.1, C49.1, C51.2, C52.1, C53.2, C54.2, C55.2, C56.1, C57.1, C58.1, C59.2, C60.2, C61.2, C62.2, C63.2, F1.2, F1.3, F1.5, J1.5, J1.6, J2.3, J2.5, J2.9, J3.5, J8.6, J8.10, J8.11, J10.12, J10.39, J10.40, Q4.3, R6.2, R7.2, R23.1, R47.1, R76.1, R79.1, R82.1, R83.1, R84.1, R87.2, RN5.3, RN5.6, RN6.2, RN6.7, SW3.2, U1.12, U1.18, U1.31, U1.47, U1.63, U2.B3, U2.C1, U2.E5, U3.3, U4.3, U7.1, U7.12, U12.1, U12.2, U13.1, U13.10, U13.11, U13.21, U14.2, U16.1, U16.5
unnamed: AE2.1, C46.1
unnamed: C43.1, F1.4
unnamed: C43.2, U7.10
unnamed: C46.2, L8.2
unnamed: C48.2, L10.1, R46.1
unnamed: C49.2, U16.4
unnamed: C51.1, C53.1, J10.6, R80.1
unnamed: C52.2, D6.1, J9.1, R78.2
unnamed: C54.1, C55.1, J10.37, J10.38, R81.1
unnamed: D1.1, R6.1
unnamed: D2.1, R7.1
unnamed: D6.2, L10.2, U16.8
unnamed: D7.1, R87.1
unnamed: F1.1, U12.6
unnamed: J9.4, U16.6
unnamed: J10.1, R84.2
unnamed: J10.2, R83.2
unnamed: J10.3, R82.2
unnamed: L8.1, U12.3
unnamed: Q4.1, R54.2
unnamed: R1.1, U2.C2
unnamed: R54.1, R75.1, R76.2, U14.4
unnamed: R78.1, R79.2, U16.7
